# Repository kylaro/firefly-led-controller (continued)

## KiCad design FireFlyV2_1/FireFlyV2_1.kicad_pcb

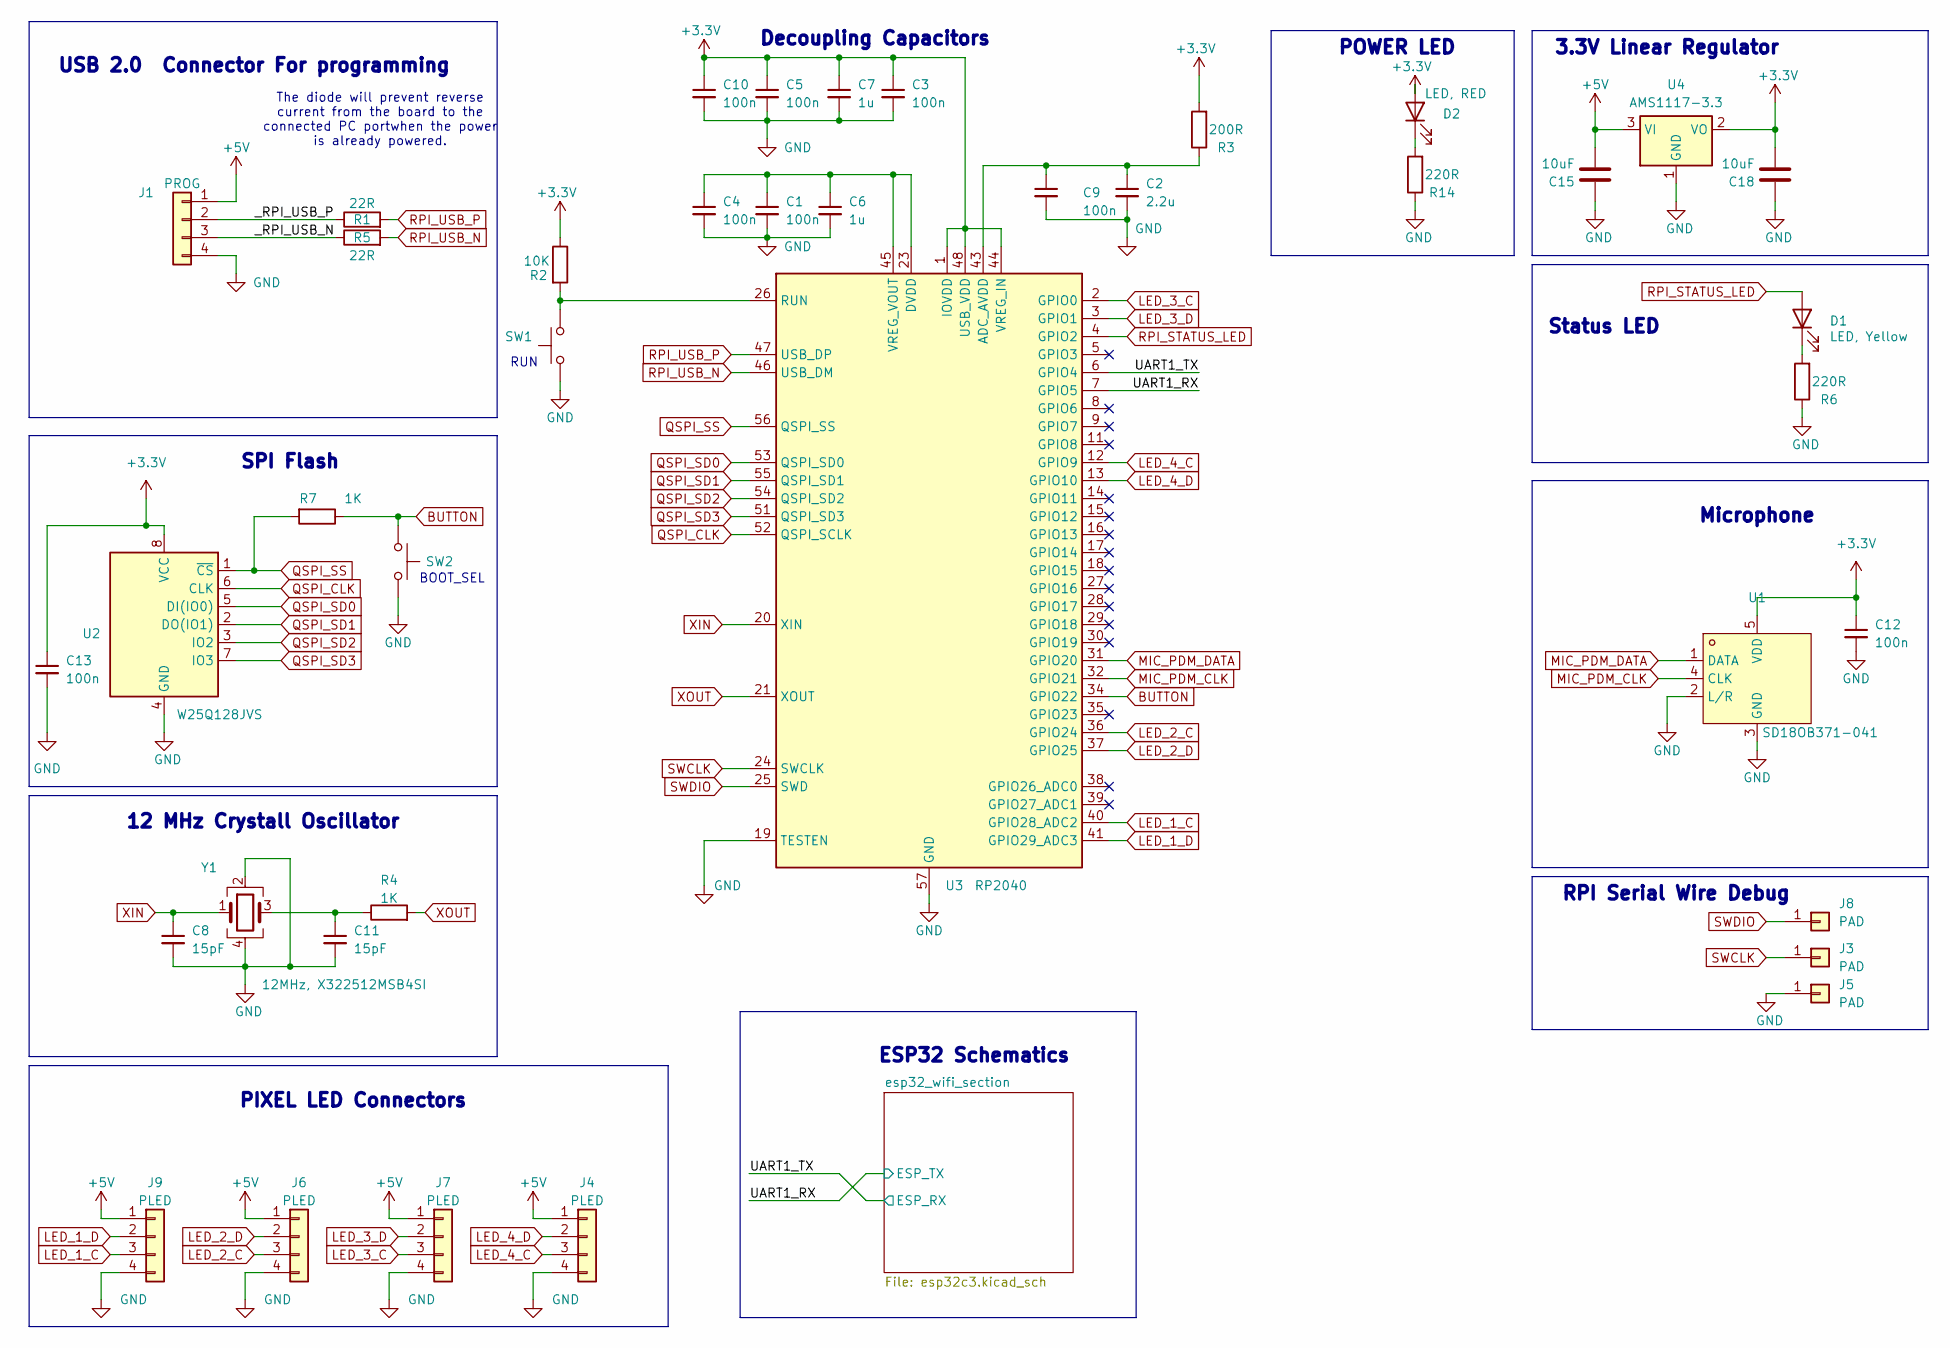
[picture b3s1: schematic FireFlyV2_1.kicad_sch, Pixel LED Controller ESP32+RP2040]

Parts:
C1, C3, C4, C5, C9, C10, C12, C13: 100n; C_0402_1005Metric; LCSC Part C1525
C2: 2.2u; C_0402_1005Metric; LCSC Part C12530
C6, C7: 1u; C_0402_1005Metric; LCSC Part C52923
C8, C11: 15pF; C_0402_1005Metric; LCSC Part C1548
C15, C18: 10uF; C_0603_1608Metric; LCSC Part C19702
D1: LED, Yellow; LED_0603_1608Metric; LCSC Part C72038
D2: LED, RED; LED_0603_1608Metric; LCSC Part C2286
J1: PROG; USB_PROG_PAD
J3, J5, J8: PAD; TestPoint_Pad_1.0x1.0mm
J4, J6, J7, J9: PLED; PIXEL-LED-PAD-4
R1, R5: 22R; R_0402_1005Metric; LCSC Part C25092
R2: 10K; R_0402_1005Metric; LCSC Part C25744
R3: 200R; R_0402_1005Metric; LCSC Part C25087
R4, R7: 1K; R_0402_1005Metric; LCSC Part C11702
R6, R14: 220R; R_0402_1005Metric; LCSC Part C25091
SW1, SW2: BTN; SW_SPST_B3U-1000P; LCSC Part C231329
U1: SD18OB371-041; RHLGA-5L_L3.5-W2.7-P0.82-MP23ABS1TR; LCSC Part C3040249
U2: W25Q128JVS; SOIC-8_5.275x5.275mm_P1.27mm; LCSC Part C97521
U3: RP2040; QFN-56-1EP_7x7mm_P0.4mm_EP3.2x3.2mm; LCSC Part C2040
U4: AMS1117-3.3; SOT-223-3_TabPin2; LCSC Part C6186
Y1: 12MHz, X322512MSB4SI; Crystal_SMD_3225-4Pin_3.2x2.5mm; LCSC Part C9002

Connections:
+3.3V: C3.1, C5.1, C7.1, C10.1, C12.1, C13.1, C18.1, D2.2 (A), R2.1, R3.2, U1.5 (VDD), U2.8 (VCC), U3.1 (IOVDD), U3.10 (IOVDD), U3.22 (IOVDD), U3.33 (IOVDD), U3.42 (IOVDD), U3.44 (VREG_IN), U3.48 (USB_VDD), U3.49 (IOVDD), U4.2 (VO); also elsewhere on the board
+5V: C15.1, J1.1, J4.1, J6.1, J7.1, J9.1, U4.3 (VI); also elsewhere on the board
/UART1_RX: U3.7 (GPIO5); also elsewhere on the board
/UART1_TX: U3.6 (GPIO4); also elsewhere on the board
/_RPI_USB_N: J1.3, R5.1
/_RPI_USB_P: J1.2, R1.1
BUTTON: R7.1, SW2.1, U3.34 (GPIO22)
GND: C1.2, C2.2, C3.2, C4.2, C5.2, C6.2, C7.2, C8.2, C9.2, C10.2, C11.2, C12.2, C13.2, C15.2, C18.2, J1.4, J4.4, J5.1, J6.4, J7.4, J9.4, R6.1, R14.1, SW1.2, SW2.2, U1.2 (L/R), U1.3 (GND), U2.4 (GND), U3.19 (TESTEN), U3.57 (GND), U4.1 (GND), Y1.2, Y1.4; also elsewhere on the board
LED_1_C: J9.3, U3.40 (GPIO28_ADC2)
LED_1_D: J9.2, U3.41 (GPIO29_ADC3)
LED_2_C: J6.3, U3.36 (GPIO24)
LED_2_D: J6.2, U3.37 (GPIO25)
LED_3_C: J7.3, U3.2 (GPIO0)
LED_3_D: J7.2, U3.3 (GPIO1)
LED_4_C: J4.3, U3.12 (GPIO9)
LED_4_D: J4.2, U3.13 (GPIO10)
MIC_PDM_CLK: U1.4 (CLK), U3.32 (GPIO21)
MIC_PDM_DATA: U1.1 (DATA), U3.31 (GPIO20)
unnamed: C11.1, R4.1, Y1.3
unnamed: D1.1 (K), R6.2
unnamed: D2.1 (K), R14.2
unnamed: C2.1, C9.1, R3.1, U3.43 (ADC_AVDD)
unnamed: R2.2, SW1.1, U3.26 (RUN)
unnamed: C1.1, C4.1, C6.1, U3.23 (DVDD), U3.45 (VREG_VOUT), U3.50 (DVDD)
QSPI_CLK: U2.6 (CLK), U3.52 (QSPI_SCLK)
QSPI_SD0: U2.5 (DI(IO0)), U3.53 (QSPI_SD0)
QSPI_SD1: U2.2 (DO(IO1)), U3.55 (QSPI_SD1)
QSPI_SD2: U2.3 (IO2), U3.54 (QSPI_SD2)
QSPI_SD3: U2.7 (IO3), U3.51 (QSPI_SD3)
QSPI_SS: R7.2, U2.1 (~CS), U3.56 (QSPI_SS)
RPI_STATUS_LED: D1.2 (A), U3.4 (GPIO2)
RPI_USB_N: R5.2, U3.46 (USB_DM)
RPI_USB_P: R1.2, U3.47 (USB_DP)
SWCLK: J3.1, U3.24 (SWCLK)
SWDIO: J8.1, U3.25 (SWD)
XIN: C8.1, U3.20 (XIN), Y1.1
XOUT: R4.2, U3.21 (XOUT)

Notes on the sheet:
3.3V Linear Regulator
Microphone
SPI Flash
RPI Serial Wire Debug
Decoupling Capacitors
POWER LED
12 MHz Crystall Oscillator
RUN
The diode will prevent reverse current from the board to the connected PC portwhen the power is already powered.
PIXEL LED Connectors
USB 2.0 Connector For programming
BOOT_SEL
Status LED
ESP32 Schematics

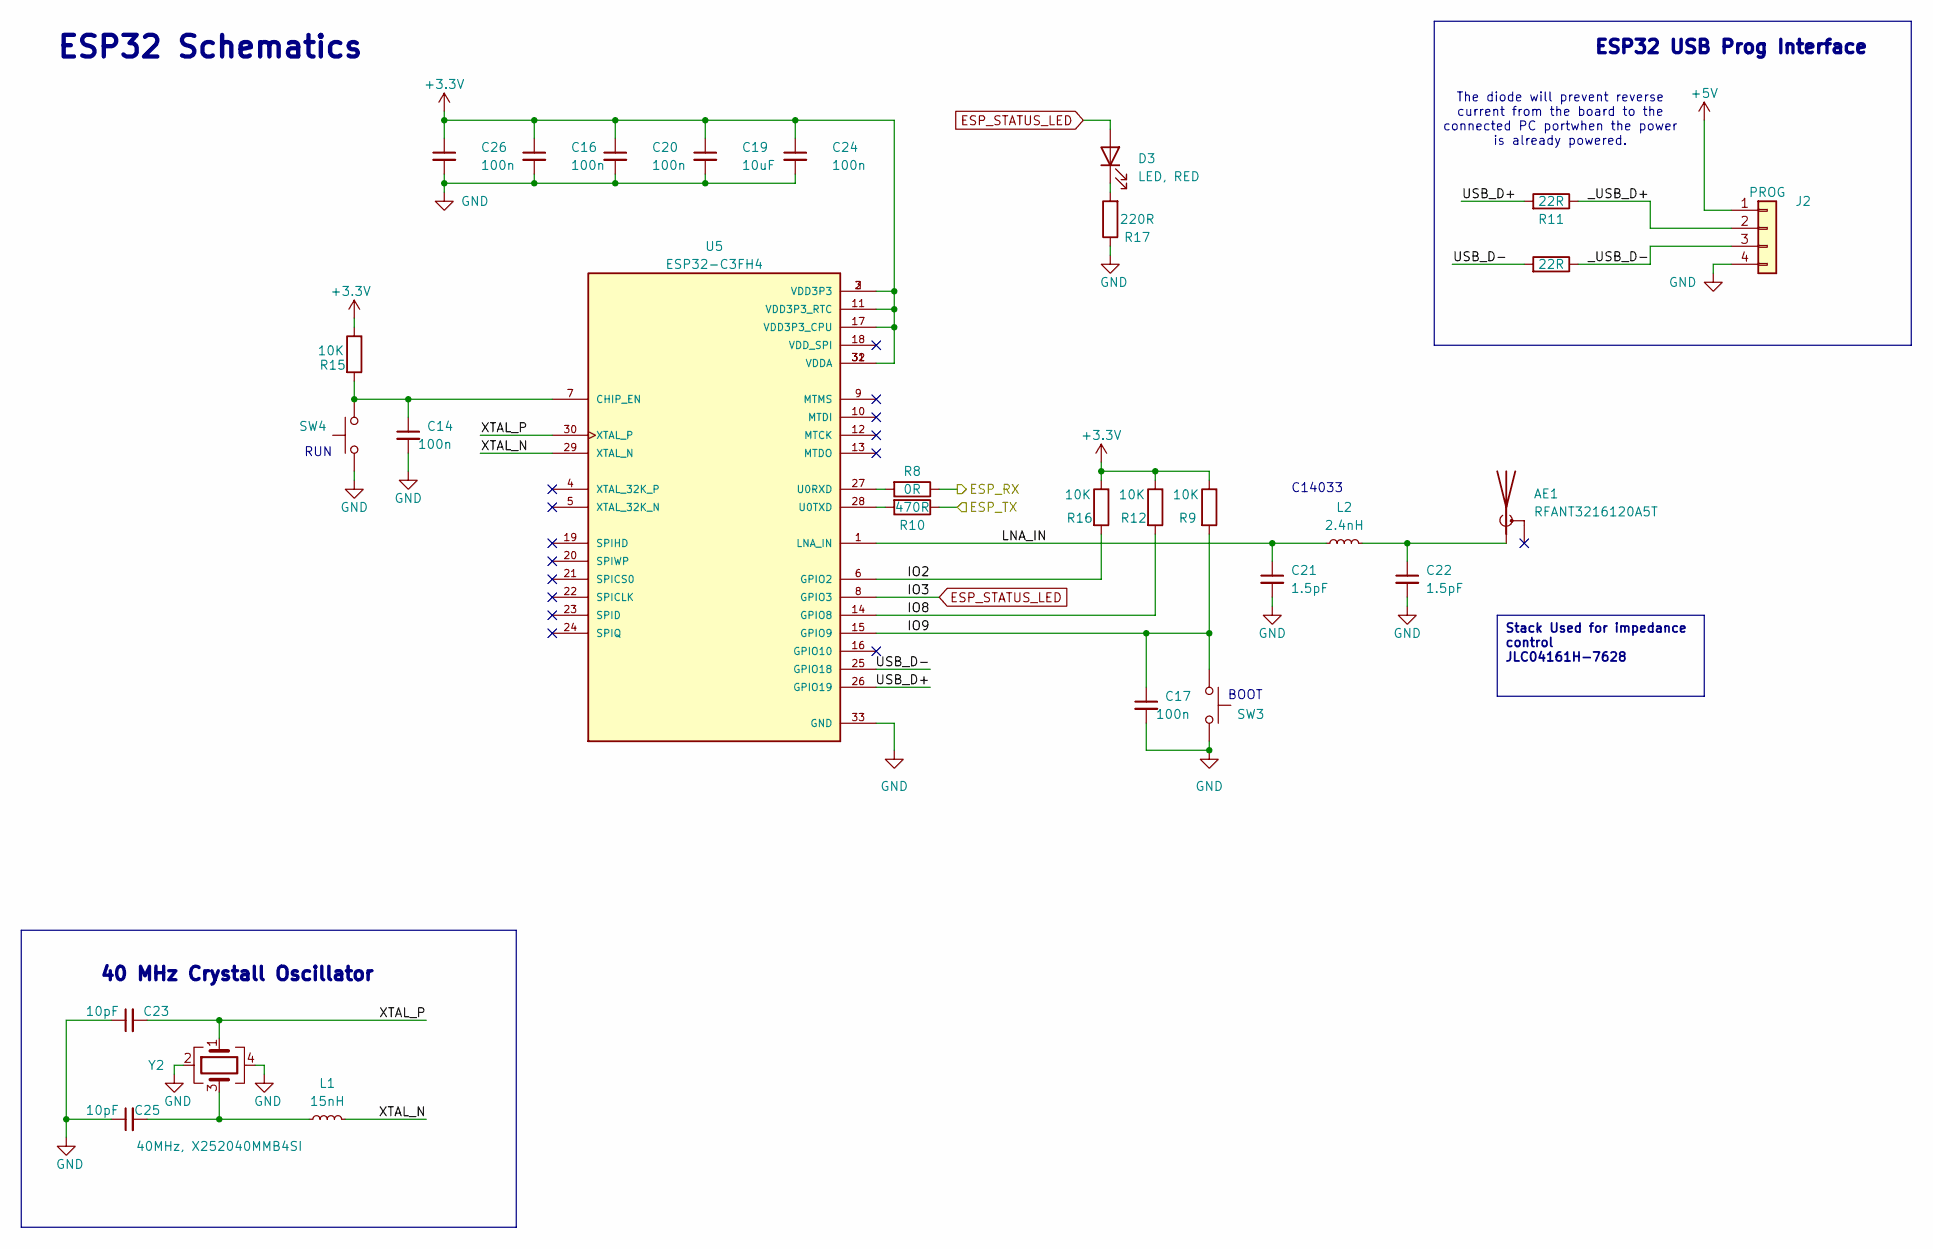
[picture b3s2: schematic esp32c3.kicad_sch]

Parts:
AE1: RFANT3216120A5T; FILTER-SMD_1206-2P-L3.2-W1.6-L; LCSC Part C293767
C14, C16, C17, C20, C24, C26: 100n; C_0402_1005Metric; LCSC Part C1525
C19: 10uF; C_0603_1608Metric; LCSC Part C19702
C21, C22: 1.5pF; C_0402_1005Metric; LCSC Part C1552
C23, C25: 10pF; C_0402_1005Metric; LCSC Part C32949
D3: LED, RED; LED_0603_1608Metric; LCSC Part C2286
J2: PROG; USB_PROG_PAD
L1: 15nH; L_0402_1005Metric; LCSC Part C27143
L2: 2.4nH; L_0402_1005Metric; LCSC Part C219526
R8: 0R; R_0402_1005Metric; LCSC Part C17168
R9, R12, R15, R16: 10K; R_0402_1005Metric; LCSC Part C25744
R10: 470R; R_0402_1005Metric; LCSC Part C25117
R11, R13: 22R; R_0402_1005Metric; LCSC Part C25092
R17: 220R; R_0402_1005Metric; LCSC Part C25091
SW3, SW4: BTN; SW_SPST_B3U-1000P; LCSC Part C231329
U5: ESP32-C3FH4; MPN ESP32-C3FH4; LCSC Part C2858491
Y2: 40MHz, X252040MMB4SI; Crystal_SMD_2520-4Pin_2.5x2.0mm; LCSC Part C2885592

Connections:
+3.3V: C16.1, C19.1, C20.1, C24.1, C26.1, R9.1, R12.1, R15.1, R16.1, U5.2 (VDD3P3), U5.3 (VDD3P3), U5.11 (VDD3P3_RTC), U5.17 (VDD3P3_CPU), U5.31 (VDDA), U5.32 (VDDA); also elsewhere on the board
+5V: J2.1; also elsewhere on the board
/UART1_RX: R10.1; also elsewhere on the board
/UART1_TX: R8.1; also elsewhere on the board
/esp32_wifi_section/IO2: R16.2, U5.6 (GPIO2)
/esp32_wifi_section/IO8: R12.2, U5.14 (GPIO8)
/esp32_wifi_section/IO9: C17.1, R9.2, SW3.2, U5.15 (GPIO9)
/esp32_wifi_section/LNA_IN: C21.1, L2.1, U5.1 (LNA_IN)
/esp32_wifi_section/USB_D+: R11.2, U5.26 (GPIO19)
/esp32_wifi_section/USB_D-: R13.2, U5.25 (GPIO18)
/esp32_wifi_section/XTAL_N: L1.2, U5.29 (XTAL_N)
/esp32_wifi_section/XTAL_P: C23.2, U5.30 (XTAL_P), Y2.1
/esp32_wifi_section/_USB_D+: J2.2, R11.1
/esp32_wifi_section/_USB_D-: J2.3, R13.1
ESP_STATUS_LED: D3.2 (A), U5.8 (GPIO3)
GND: C14.2, C16.2, C17.2, C19.2, C20.2, C21.2, C22.2, C23.1, C24.2, C25.1, C26.2, J2.4, R17.1, SW3.1, SW4.2, U5.33 (GND), Y2.2, Y2.4; also elsewhere on the board
unnamed: AE1.1 (A), C22.1, L2.2
unnamed: C25.2, L1.1, Y2.3
unnamed: D3.1 (K), R17.2
unnamed: C14.1, R15.2, SW4.1, U5.7 (CHIP_EN)
unnamed: R8.2, U5.27 (U0RXD)
unnamed: R10.2, U5.28 (U0TXD)

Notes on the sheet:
Stack Used for impedance control JLC04161H-7628
40 MHz Crystall Oscillator
RUN
The diode will prevent reverse current from the board to the connected PC portwhen the power is already powered.
ESP32 Schematics
C14033
ESP32 USB Prog Interface
BOOT

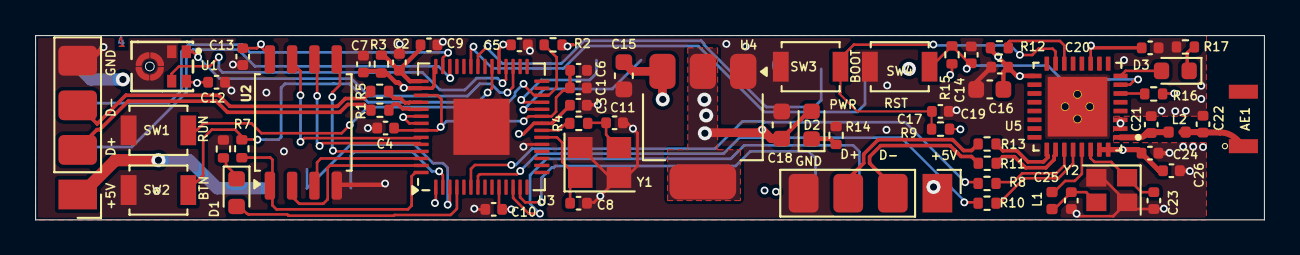
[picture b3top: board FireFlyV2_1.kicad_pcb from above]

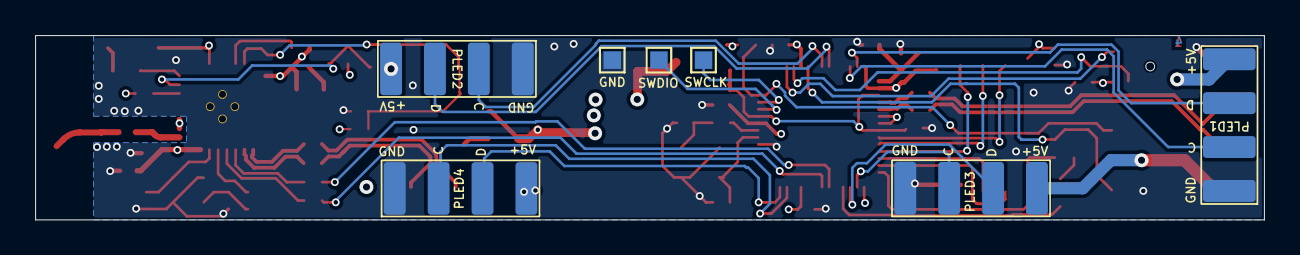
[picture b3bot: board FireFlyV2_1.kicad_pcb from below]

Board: 4 copper layers, 70.0 x 10.5 mm, 69 parts (7 on the bottom side), 54 nets.

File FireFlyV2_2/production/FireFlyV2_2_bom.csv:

Designator,Footprint,Quantity,Value,LCSC Part #
AE1,FILTER-SMD_1206-2P-L3.2-W1.6-L,1,RFANT3216120A5T,C127629
"C1, C10, C12, C13, C16, C20, C24, C26, C3, C4, C5, C9",0402,12,100n,C1525
"C11, C8",0402,2,15pF,C1548
"C15, C18, C19",0603,3,10uF,C19702
C2,0402,1,2.2u,C12530
"C21, C22",0402,2,1.5pF,C1552
"C23, C25",0402,2,10pF,C32949 
"C6, C7",0402,2,1u,C52923
D1,0603,1,"LED, Yellow",C72038
D3,0603,1,"LED, RED",C2286
L1,0402,1,2.7nH, C98058
L2,0402,1,6.8nH,C77110
MIC1,LGA-6_L4.7-W3.8-P1.65_LMD4737T,1,LMD4737T263-OY1,C5373239
"R1, R11, R13, R5",0402,4,22R,C25092
R10,0402,1,470R,C25117 
"R12, R15, R16, R2, R9",0402,5,10K,C25744
"R17, R6",0402,2,220R,C25091
R3,0402,1,200R,C25087
R4,0402,1,1K,C11702
R8,0402,1,0R,C17168 
U2,SOIC-8_5.275x5.275mm_P1.27mm,1,W25Q128JVS, C97521
U3,QFN-56-1EP_7x7mm_P0.4mm_EP3.2x3.2mm,1,RP2040,C2040
U4,SOT-223-3_TabPin2,1,AMS1117-3.3,C6186
U5,ESP32-C3FH4,1,ESP32-C3FH4,C2858491
Y1,Crystal_SMD_3225-4Pin_3.2x2.5mm,1,"12MHz, X322512MSB4SI",C9002
Y2,Crystal_SMD_2520-4Pin_2.5x2.0mm,1,"40MHz, X252040MMB4SI",C2885592

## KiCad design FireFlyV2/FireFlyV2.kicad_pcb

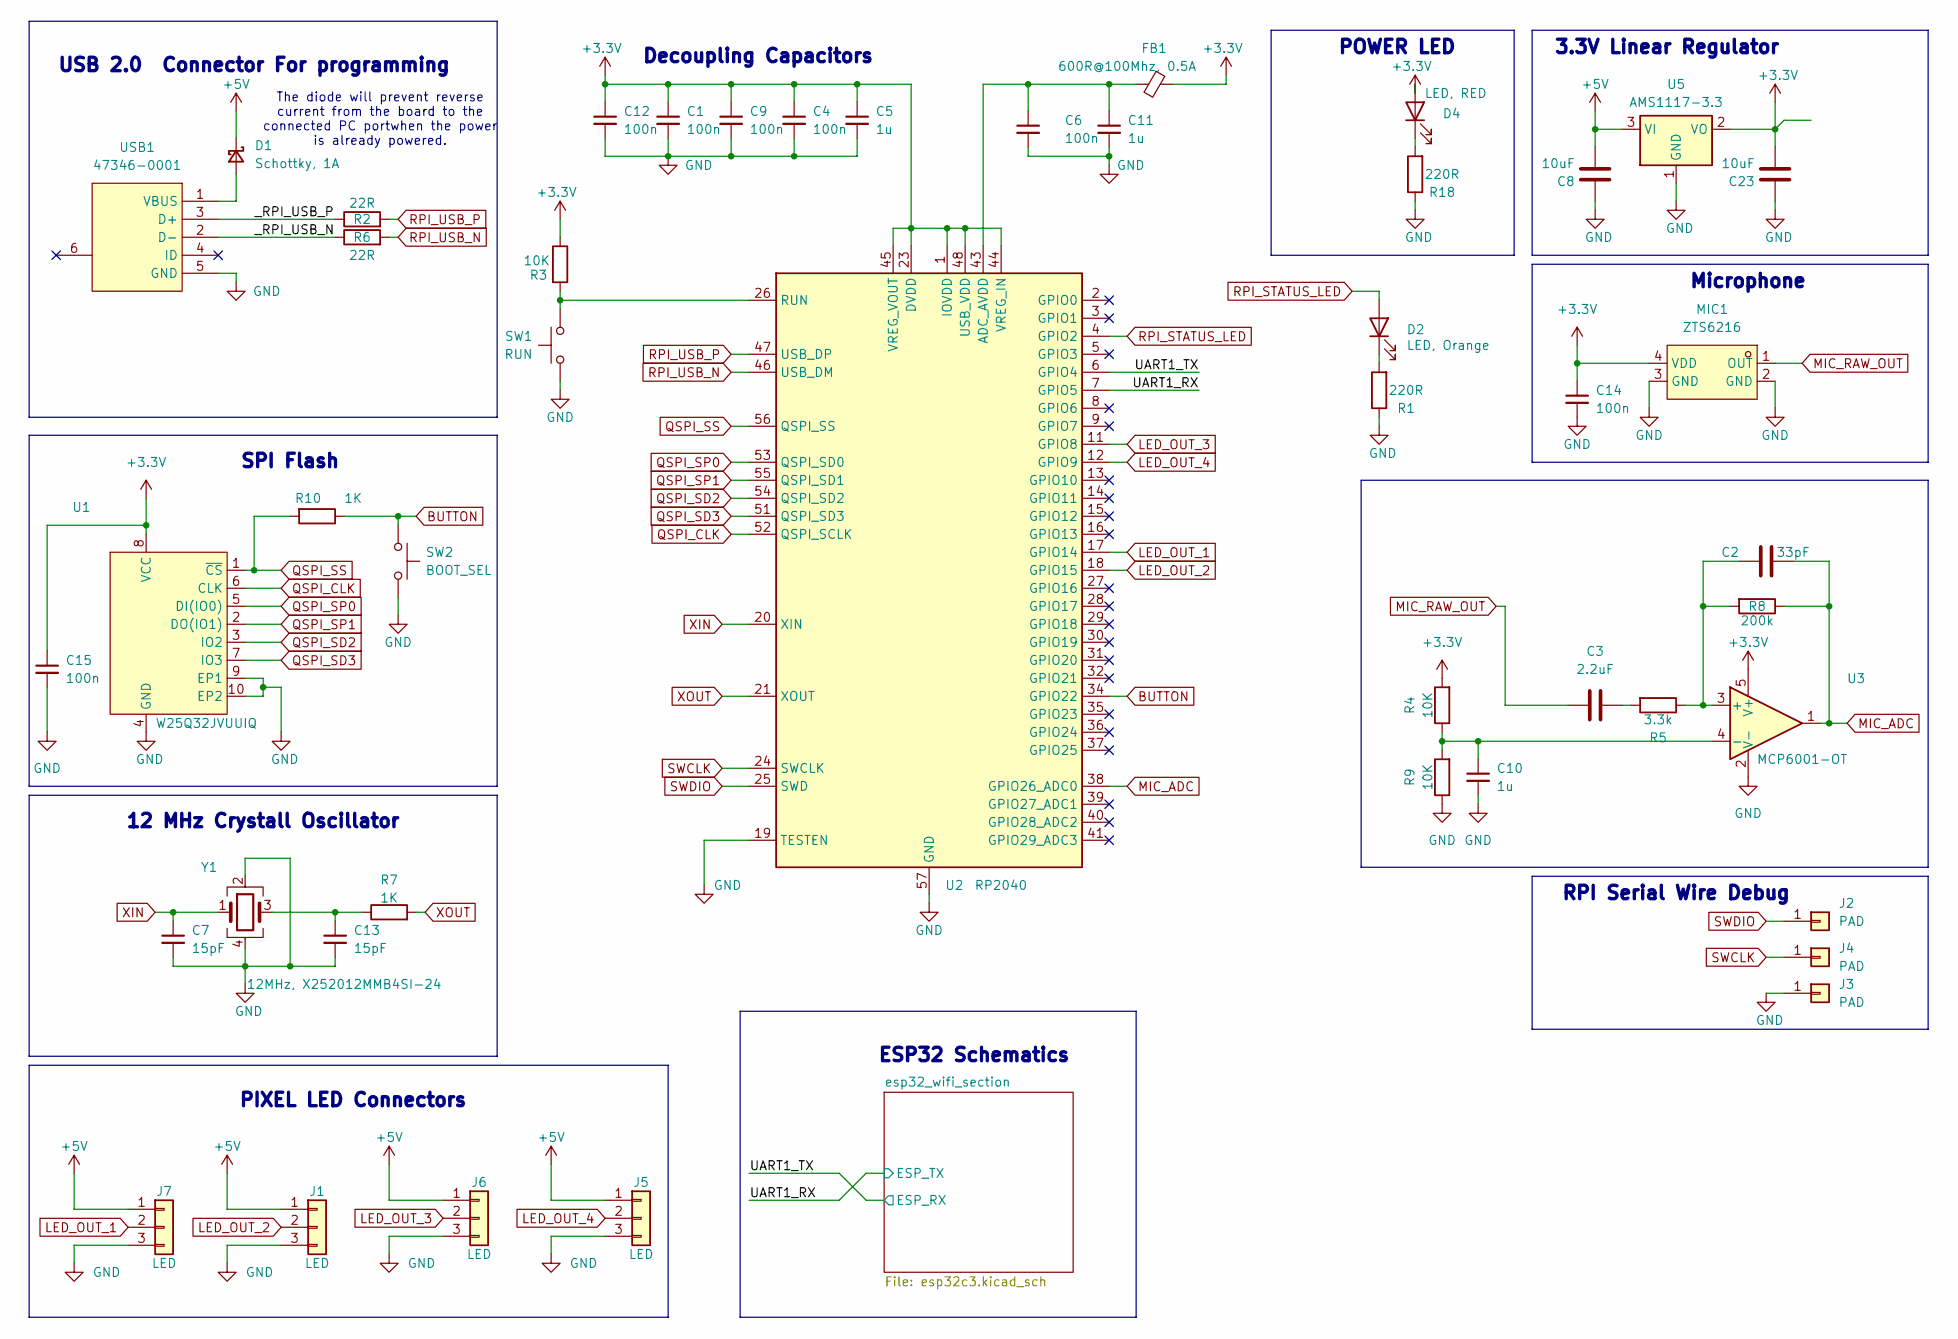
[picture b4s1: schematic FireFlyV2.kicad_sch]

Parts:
C1, C4, C6, C9, C12, C14, C15: 100n; C_0402_1005Metric; LCSC Part C1525
C2: 33pF; C_0402_1005Metric; LCSC Part C1562
C3: 2.2uF; C_0402_1005Metric; LCSC Part C12530
C5, C10, C11: 1u; C_0402_1005Metric; LCSC Part C52923
C7, C13: 15pF; C_0402_1005Metric; LCSC Part C1548
C8, C23: 10uF; C_0603_1608Metric; LCSC Part C385035
D1: Schottky, 1A; D_SOD-123F; LCSC Part C2900731
D2: LED, Orange; LED_0402_1005Metric; LCSC Part C273599
D4: LED, RED; LED_0402_1005Metric; LCSC Part C71911
FB1: 600R@100Mhz, 0.5A; L_0402_1005Metric; LCSC Part C96722
J1, J5, J6, J7: LED; PIXEL-LED-PAD
J2, J3, J4: PAD; TestPoint_Pad_1.0x1.0mm
MIC1: ZTS6216; MIC-SMD_4P-L2.8-W1.9-P1.84-TL; LCSC Part C481302
R1, R18: 220R; R_0402_1005Metric; LCSC Part C25091
R2, R6: 22R; R_0402_1005Metric; LCSC Part C25092
R3, R4, R9: 10K; R_0402_1005Metric; LCSC Part C25744
R5: 3.3k; R_0402_1005Metric; LCSC Part C25890
R7, R10: 1K; R_0402_1005Metric; LCSC Part C11702
R8: 200k; R_0402_1005Metric; LCSC Part C25764
SW1: RUN; SW_SPST_B3U-1000P; LCSC Part C231329
SW2: BOOT_SEL; SW_SPST_B3U-1000P; LCSC Part C231329
U1: W25Q32JVUUIQ; USON-8_L4.0-W3.0-P0.80-BL_WINBOND_UU; LCSC Part C2999380
U2: RP2040; QFN-56-1EP_7x7mm_P0.4mm_EP3.2x3.2mm; LCSC Part C2040
U3: MCP6001-OT; SOT-23-5; LCSC Part C116490
U5: AMS1117-3.3; SOT-223-3_TabPin2; LCSC Part C6186
USB1: 47346-0001; MICRO-USB-SMD_47346-0001; LCSC Part C132560
Y1: 12MHz, X252012MMB4SI-24; Crystal_SMD_2520-4Pin_2.5x2.0mm; LCSC Part C2896601

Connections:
+3.3V: C1.1, C4.1, C5.1, C9.1, C12.1, C14.1, C15.1, C23.1, D4.2 (A), FB1.1, MIC1.4 (VDD), R3.1, R4.2, U1.8 (VCC), U2.1 (IOVDD), U2.10 (IOVDD), U2.22 (IOVDD), U2.23 (DVDD), U2.33 (IOVDD), U2.42 (IOVDD), U2.44 (VREG_IN), U2.45 (VREG_VOUT), U2.48 (USB_VDD), U2.49 (IOVDD), U2.50 (DVDD), U3.5 (V+), U5.2 (VO); also elsewhere on the board
+5V: C8.1, D1.1 (K), J1.1, J5.1, J6.1, J7.1, U5.3 (VI); also elsewhere on the board
/UART1_RX: U2.7 (GPIO5); also elsewhere on the board
/UART1_TX: U2.6 (GPIO4); also elsewhere on the board
/_RPI_USB_N: R6.1, USB1.2 (D-)
/_RPI_USB_P: R2.1, USB1.3 (D+)
BUTTON: R10.1, SW2.1, U2.34 (GPIO22)
GND: C1.2, C4.2, C5.2, C6.2, C7.2, C8.2, C9.2, C10.2, C11.2, C12.2, C13.2, C14.2, C15.2, C23.2, J1.3, J3.1, J5.3, J6.3, J7.3, MIC1.2 (GND), MIC1.3 (GND), R1.1, R9.1, R18.1, SW1.2, SW2.2, U1.4 (GND), U1.9 (EP1), U1.10 (EP2), U2.19 (TESTEN), U2.57 (GND), U3.2 (V-), U5.1 (GND), USB1.5 (GND), Y1.2, Y1.4; also elsewhere on the board
LED_OUT_1: J7.2, U2.17 (GPIO14)
LED_OUT_2: J1.2, U2.18 (GPIO15)
LED_OUT_3: J6.2, U2.11 (GPIO8)
LED_OUT_4: J5.2, U2.12 (GPIO9)
MIC_ADC: C2.2, R8.1, U2.38 (GPIO26_ADC0), U3.1
MIC_RAW_OUT: C3.1, MIC1.1 (OUT)
unnamed: C3.2, R5.2
unnamed: C13.1, R7.1, Y1.3
unnamed: D1.2 (A), USB1.1 (VBUS)
unnamed: D2.1 (K), R1.2
unnamed: D4.1 (K), R18.2
unnamed: C6.1, C11.1, FB1.2, U2.43 (ADC_AVDD)
unnamed: R3.2, SW1.1, U2.26 (RUN)
unnamed: C2.1, R5.1, R8.2, U3.3 (+)
unnamed: C10.1, R4.1, R9.2, U3.4 (-)
QSPI_CLK: U1.6 (CLK), U2.52 (QSPI_SCLK)
QSPI_SD2: U1.3 (IO2), U2.54 (QSPI_SD2)
QSPI_SD3: U1.7 (IO3), U2.51 (QSPI_SD3)
QSPI_SP0: U1.5 (DI(IO0)), U2.53 (QSPI_SD0)
QSPI_SP1: U1.2 (DO(IO1)), U2.55 (QSPI_SD1)
QSPI_SS: R10.2, U1.1 (~CS), U2.56 (QSPI_SS)
RPI_STATUS_LED: D2.2 (A), U2.4 (GPIO2)
RPI_USB_N: R6.2, U2.46 (USB_DM)
RPI_USB_P: R2.2, U2.47 (USB_DP)
SWCLK: J4.1, U2.24 (SWCLK)
SWDIO: J2.1, U2.25 (SWD)
XIN: C7.1, U2.20 (XIN), Y1.1
XOUT: R7.2, U2.21 (XOUT)

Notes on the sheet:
3.3V Linear Regulator
Microphone
SPI Flash
RPI Serial Wire Debug
Decoupling Capacitors
POWER LED
12 MHz Crystall Oscillator
The diode will prevent reverse current from the board to the connected PC portwhen the power is already powered.
PIXEL LED Connectors
USB 2.0 Connector For programming
ESP32 Schematics

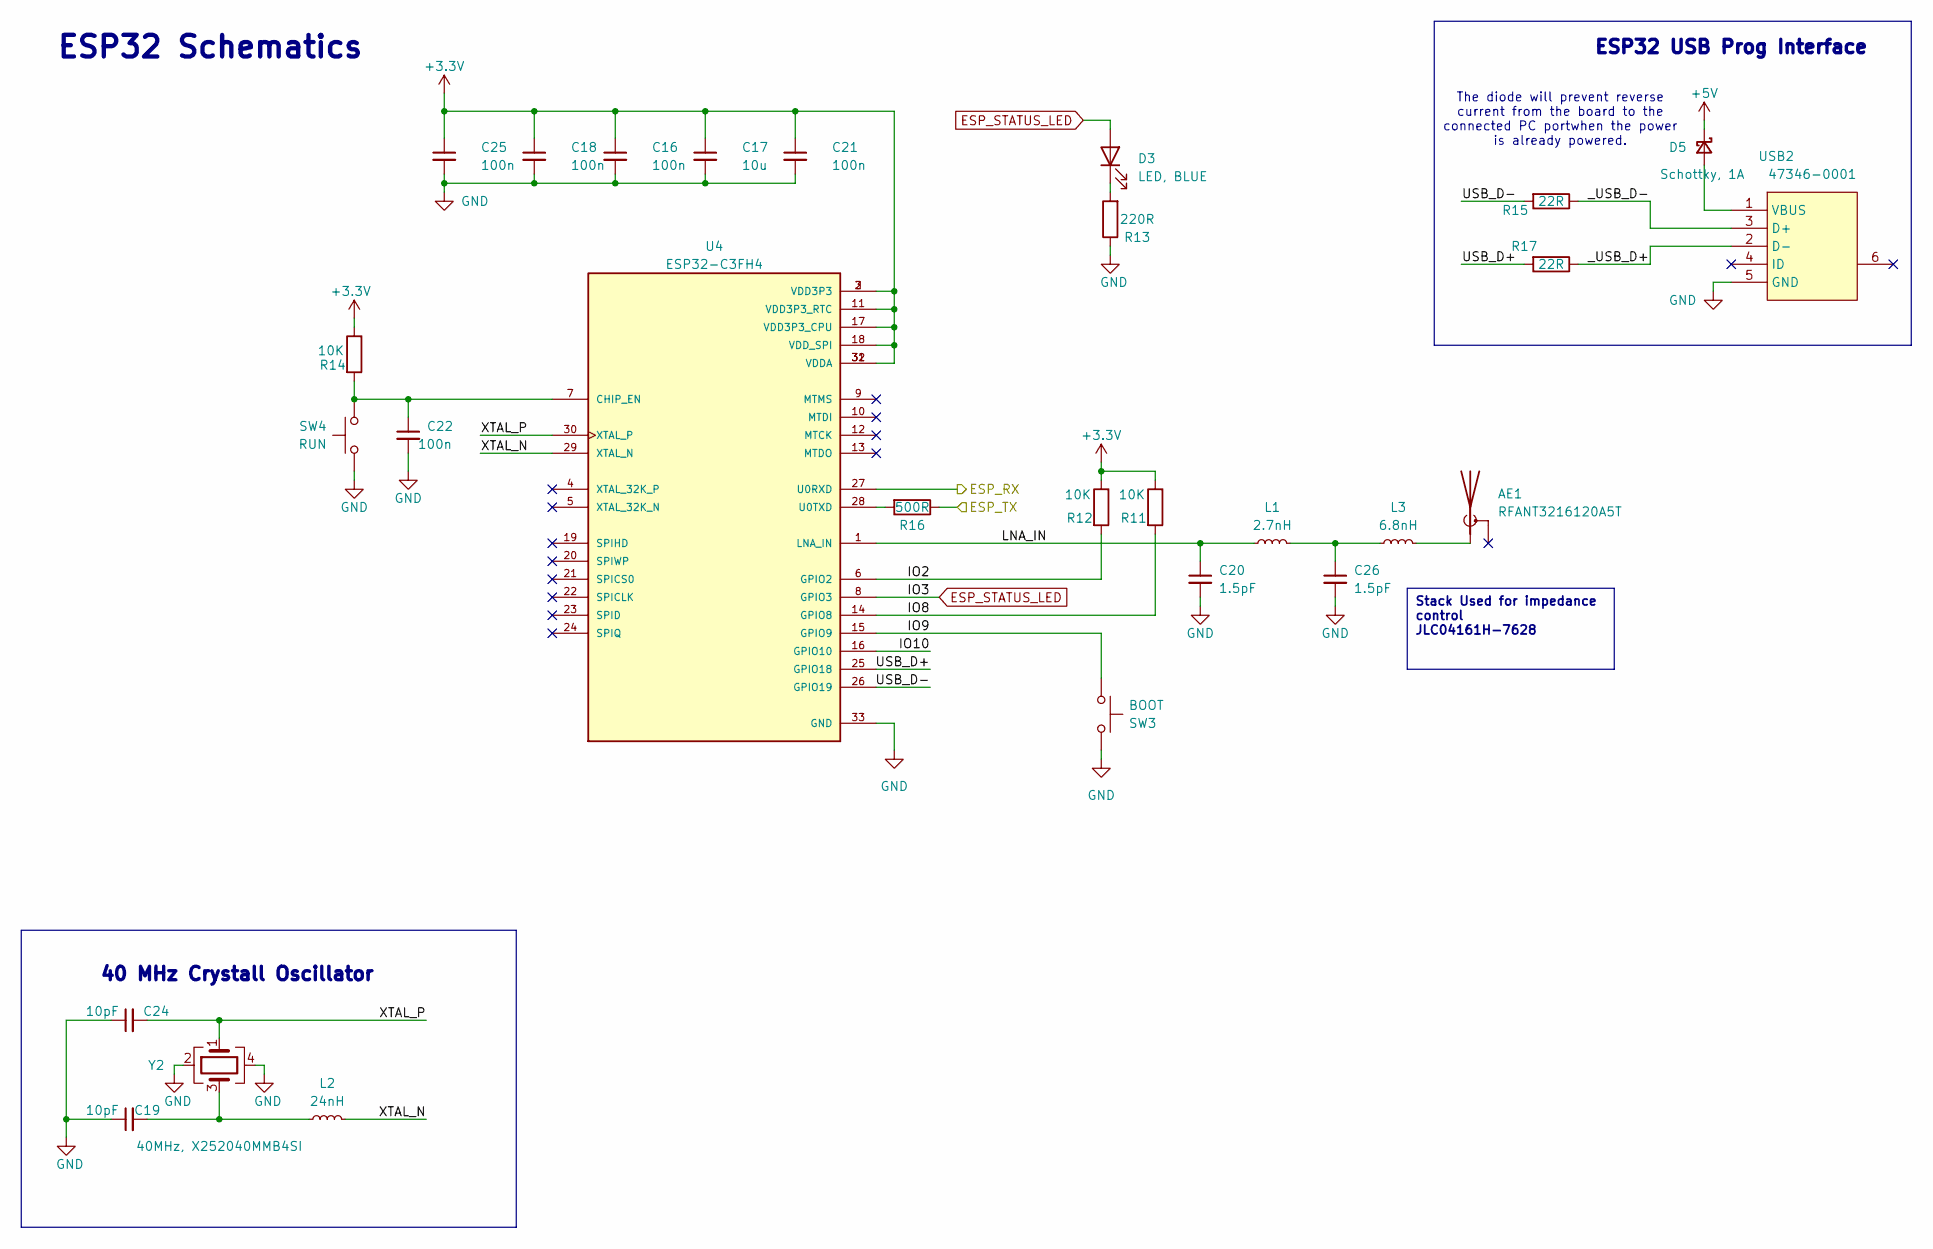
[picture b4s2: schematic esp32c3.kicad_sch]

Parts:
AE1: RFANT3216120A5T; FILTER-SMD_1206-2P-L3.2-W1.6-L; LCSC Part C127629
C16, C18, C21, C22, C25: 100n; C_0402_1005Metric; LCSC Part C1525
C17: 10u; C_0603_1608Metric; LCSC Part C385035
C19, C24: 10pF; C_0402_1005Metric; LCSC Part C696913
C20, C26: 1.5pF; C_0402_1005Metric; LCSC Part C76900
D3: LED, BLUE; LED_0402_1005Metric; LCSC Part C7496802
D5: Schottky, 1A; D_SOD-123F; LCSC Part C2900731
L1: 2.7nH; L_0402_1005Metric; LCSC Part C98058
L2: 24nH; L_0402_1005Metric; LCSC Part C341784
L3: 6.8nH; L_0402_1005Metric; LCSC Part C77110
R11, R12, R14: 10K; R_0402_1005Metric; LCSC Part C25744
R13: 220R; R_0402_1005Metric; LCSC Part C25091
R15, R17: 22R; R_0402_1005Metric; LCSC Part C25092
R16: 500R; R_0402_1005Metric; LCSC Part C77110
SW3: BOOT; SW_SPST_B3U-1000P; LCSC Part C231329
SW4: RUN; SW_SPST_B3U-1000P; LCSC Part C231329
U4: ESP32-C3FH4; MPN ESP32-C3FH4; LCSC Part C2858491
USB2: 47346-0001; MICRO-USB-SMD_47346-0001; LCSC Part C132560
Y2: 40MHz, X252040MMB4SI; Crystal_SMD_2520-4Pin_2.5x2.0mm; LCSC Part C2885592

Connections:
+3.3V: C16.1, C17.1, C18.1, C21.1, C25.1, R11.1, R12.1, R14.1, U4.2 (VDD3P3), U4.3 (VDD3P3), U4.11 (VDD3P3_RTC), U4.17 (VDD3P3_CPU), U4.18 (VDD_SPI), U4.31 (VDDA), U4.32 (VDDA); also elsewhere on the board
+5V: D5.1 (K); also elsewhere on the board
/UART1_RX: R16.1; also elsewhere on the board
/UART1_TX: U4.27 (U0RXD); also elsewhere on the board
/esp32_wifi_section/IO2: R12.2, U4.6 (GPIO2)
/esp32_wifi_section/IO8: R11.2, U4.14 (GPIO8)
/esp32_wifi_section/IO9: SW3.2, U4.15 (GPIO9)
/esp32_wifi_section/IO10: U4.16 (GPIO10)
/esp32_wifi_section/LNA_IN: C20.1, L1.1, U4.1 (LNA_IN)
/esp32_wifi_section/USB_D+: R17.2, U4.25 (GPIO18)
/esp32_wifi_section/USB_D-: R15.2, U4.26 (GPIO19)
/esp32_wifi_section/XTAL_N: L2.2, U4.29 (XTAL_N)
/esp32_wifi_section/XTAL_P: C24.2, U4.30 (XTAL_P), Y2.1
/esp32_wifi_section/_USB_D+: R17.1, USB2.2 (D-)
/esp32_wifi_section/_USB_D-: R15.1, USB2.3 (D+)
ESP_STATUS_LED: D3.2 (A), U4.8 (GPIO3)
GND: C16.2, C17.2, C18.2, C19.1, C20.2, C21.2, C22.2, C24.1, C25.2, C26.2, R13.1, SW3.1, SW4.2, U4.33 (GND), USB2.5 (GND), Y2.2, Y2.4; also elsewhere on the board
unnamed: AE1.1 (A), L3.2
unnamed: C19.2, L2.1, Y2.3
unnamed: C26.1, L1.2, L3.1
unnamed: D3.1 (K), R13.2
unnamed: D5.2 (A), USB2.1 (VBUS)
unnamed: C22.1, R14.2, SW4.1, U4.7 (CHIP_EN)
unnamed: R16.2, U4.28 (U0TXD)

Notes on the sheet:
Stack Used for impedance control JLC04161H-7628
40 MHz Crystall Oscillator
The diode will prevent reverse current from the board to the connected PC portwhen the power is already powered.
ESP32 Schematics
ESP32 USB Prog Interface

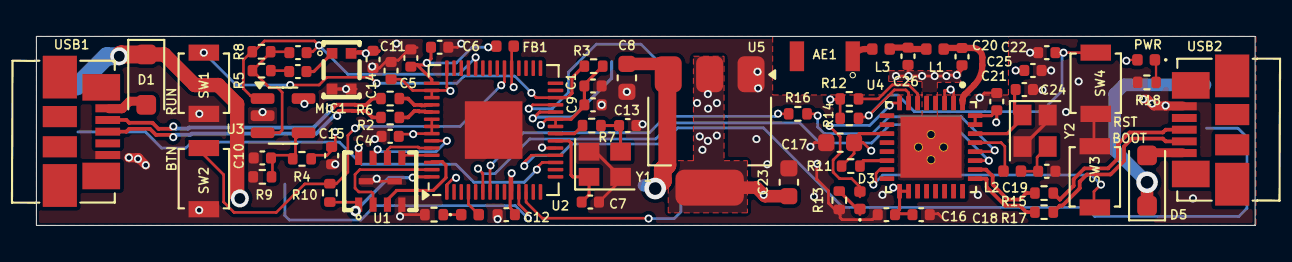
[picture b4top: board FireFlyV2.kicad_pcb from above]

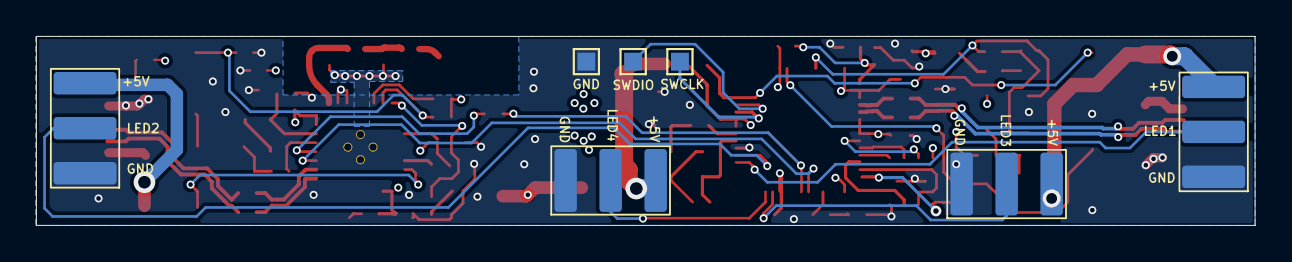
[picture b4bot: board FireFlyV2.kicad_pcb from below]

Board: 4 copper layers, 67.7 x 10.5 mm, 75 parts (7 on the bottom side), 54 nets.
